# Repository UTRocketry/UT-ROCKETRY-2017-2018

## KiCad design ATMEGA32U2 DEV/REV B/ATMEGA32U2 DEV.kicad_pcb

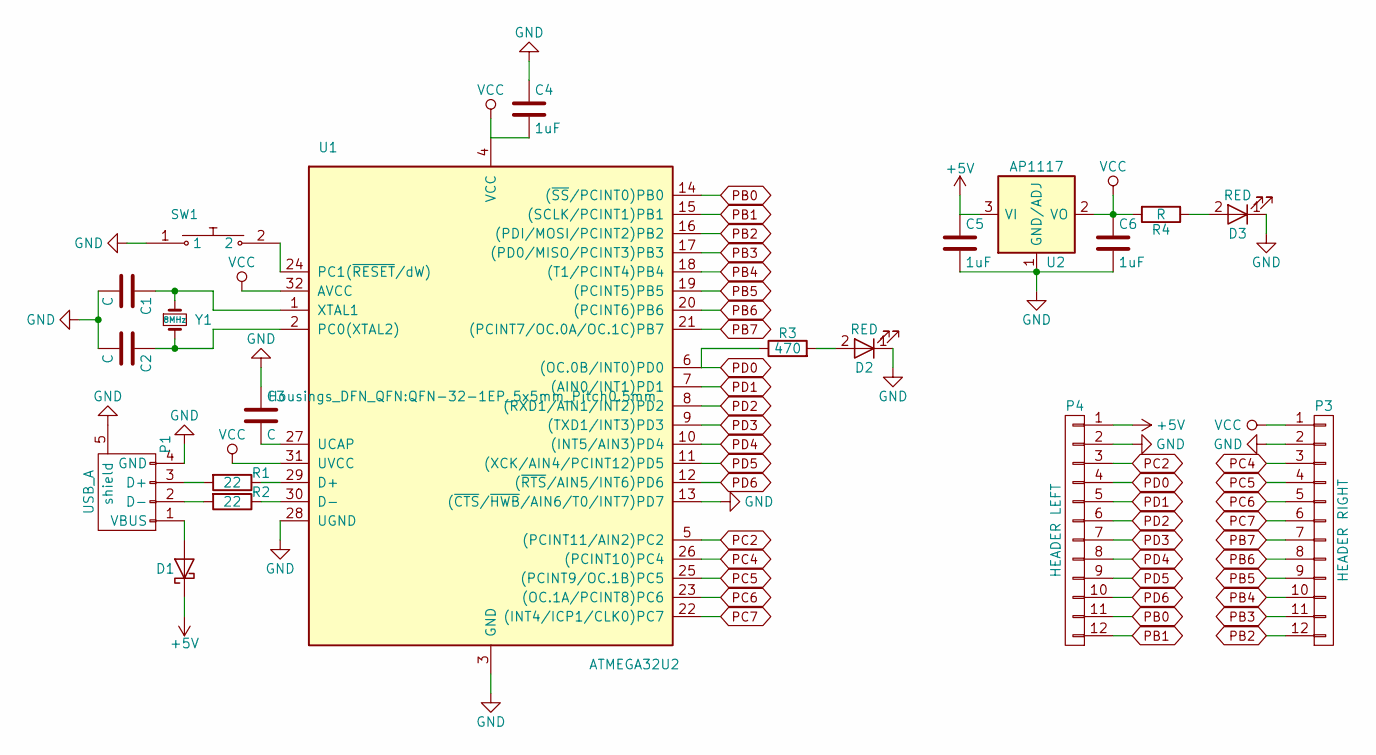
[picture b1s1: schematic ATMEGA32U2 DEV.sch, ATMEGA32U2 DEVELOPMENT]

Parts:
C1, C2, C3: C; C_0603
C4, C5, C6: 1uF; C_0603
D1: D_Schottky; D_SOD-323F
D2, D3: RED; LED_0603
P1: USB_A; USB_Micro-B_Molex_47346-0001
P3: HEADER RIGHT; Pin_Header_Straight_1x12
P4: HEADER LEFT; Pin_Header_Straight_1x12
R1, R2: 22; R_0603
R3: 470; R_0603
R4: R; R_0603
SW1: Push_SW; PTS810 SJK 250 SMTR LFS
U1: ATMEGA32U2; QFN-32-1EP_5x5mm_Pitch0.5mm
U2: AP1117; SOT-23
Y1: 8MHz; ABM3

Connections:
+5V: C5.1, D1.1 (K), P4.1, U2.3 (VI)
GND: C1.2, C2.2, C3.1, C4.1, C5.2, C6.2, D2.1 (K), D3.1 (K), P1.4 (GND), P1.5 (shield), P3.2, P4.2, SW1.1, U1.3 (GND), U1.13 ((~CTS~/~HWB~/AIN6/T0/INT7)PD7), U1.28 (UGND), U2.1 (GND/ADJ)
unnamed: C1.1, U1.1 (XTAL1), Y1.1
unnamed: C2.1, U1.2 (PC0(XTAL2)), Y1.2
unnamed: C3.2, U1.27 (UCAP)
unnamed: D1.2 (A), P1.1 (VBUS)
unnamed: D2.2 (A), R3.2
unnamed: D3.2 (A), R4.1
unnamed: P1.2 (D-), R2.2
unnamed: P1.3 (D+), R1.2
unnamed: R1.1, U1.29 (D+)
unnamed: R2.1, U1.30 (D-)
unnamed: SW1.2, U1.24 (PC1(~RESET~/dW))
PB0: P4.11, U1.14 ((~SS~/PCINT0)PB0)
PB1: P4.12, U1.15 ((SCLK/PCINT1)PB1)
PB2: P3.12, U1.16 ((PDI/MOSI/PCINT2)PB2)
PB3: P3.11, U1.17 ((PD0/MISO/PCINT3)PB3)
PB4: P3.10, U1.18 ((T1/PCINT4)PB4)
PB5: P3.9, U1.19 ((PCINT5)PB5)
PB6: P3.8, U1.20 ((PCINT6)PB6)
PB7: P3.7, U1.21 ((PCINT7/OC.0A/OC.1C)PB7)
PC2: P4.3, U1.5 ((PCINT11/AIN2)PC2)
PC4: P3.3, U1.26 ((PCINT10)PC4)
PC5: P3.4, U1.25 ((PCINT9/OC.1B)PC5)
PC6: P3.5, U1.23 ((OC.1A/PCINT8)PC6)
PC7: P3.6, U1.22 ((INT4/ICP1/CLK0)PC7)
PD0: P4.4, R3.1, U1.6 ((OC.0B/INT0)PD0)
PD1: P4.5, U1.7 ((AIN0/INT1)PD1)
PD2: P4.6, U1.8 ((RXD1/AIN1/INT2)PD2)
PD3: P4.7, U1.9 ((TXD1/INT3)PD3)
PD4: P4.8, U1.10 ((INT5/AIN3)PD4)
PD5: P4.9, U1.11 ((XCK/AIN4/PCINT12)PD5)
PD6: P4.10, U1.12 ((~RTS~/AIN5/INT6)PD6)
VCC: C4.2, C6.1, P3.1, R4.2, U1.4 (VCC), U1.31 (UVCC), U1.32 (AVCC), U2.2 (VO), U2.4 (VO)

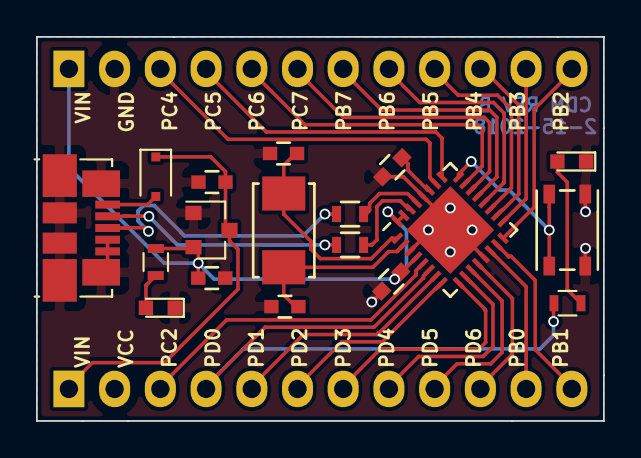
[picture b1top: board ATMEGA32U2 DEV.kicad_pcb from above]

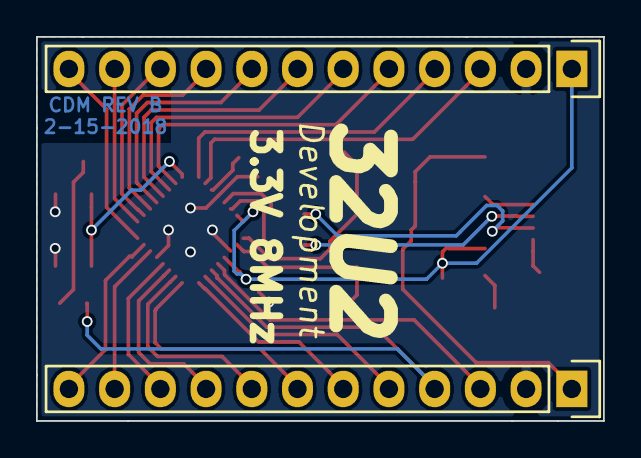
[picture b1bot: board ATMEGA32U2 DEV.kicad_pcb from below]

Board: 2 copper layers, 31.5 x 21.3 mm, 20 parts (2 on the bottom side), 34 nets.

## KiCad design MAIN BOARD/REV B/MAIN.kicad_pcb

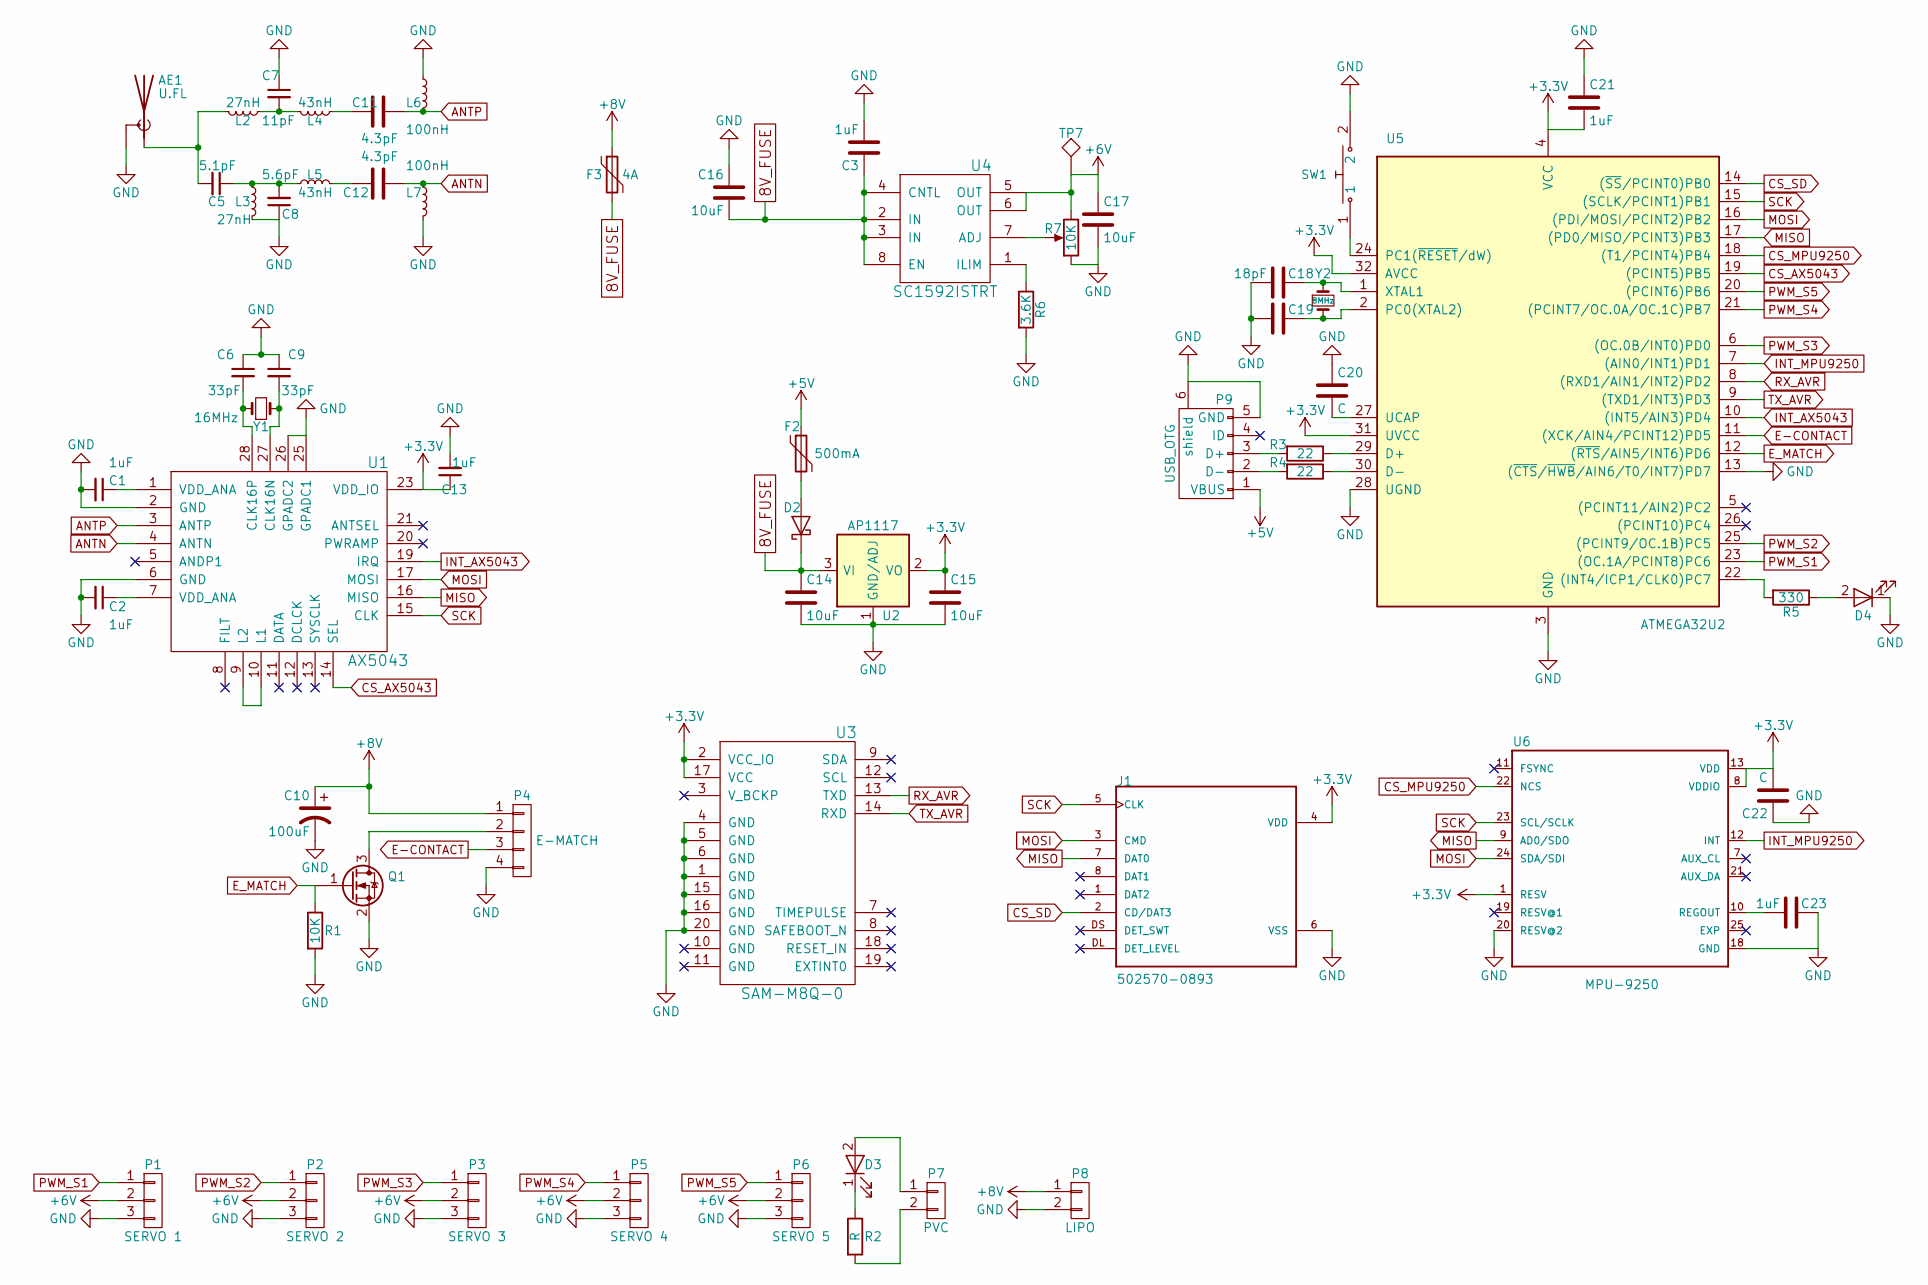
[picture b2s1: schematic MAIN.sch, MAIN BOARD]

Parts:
AE1: U.FL; U.FL-COAX
C1, C2, C3, C13, C21, C23: 1uF; C_0402
C5: 5.1pF; C_0402
C6, C9: 33pF; C_0402
C7: 11pF; C_0402
C8: 5.6pF; C_0402
C10: 100uF; C_0603
C11, C12: 4.3pF; C_0402
C14, C15, C16, C17: 10uF; C_0603
C18: 18pF; C_0402
C19, C20, C22: C; C_0402
D2: D_Schottky; D_SOD-123F
D3, D4: LED; LED_0402
F2: 500mA; C_1206
F3: 4A; C_1206
J1: 502570-0893; MOLEX_502570-0893
L2, L3: 27nH; C_0402
L4, L5: 43nH; C_0402
L6, L7: 100nH; C_0402
P1: SERVO 1; Pin_Header_Straight_1x03_Pitch2.54mm
P2: SERVO 2; Pin_Header_Straight_1x03_Pitch2.54mm
P3: SERVO 3; Pin_Header_Straight_1x03_Pitch2.54mm
P4: E-MATCH; TE1X4
P5: SERVO 4; Pin_Header_Straight_1x03_Pitch2.54mm
P6: SERVO 5; Pin_Header_Straight_1x03_Pitch2.54mm
P7: PVC; TE1X2
P8: LIPO; TE1X2
P9: USB_OTG; 0473461001_GLUE
Q1: Q_NMOS_GSD; SOT-23
R1: 10K; R_0402
R2: R; R_0402
R3, R4: 22; R_0402
R5: 330; R_0402
R6: 3.6K; R_0402
R7: 10K; Potentiometer_Trimmer-EVM3E
SW1: Push_SW; KXT 131 LHS
TP7: TEST; Measurement_Point_Round-SMD-Pad_Small
U1: AX5043; QFN-28-1EP_5x5mm_Pitch0.5mm
U2: AP1117; SOT-23
U3: SAM-M8Q-0
U4: SC1592ISTRT; SOIC-8-1EP_3.9x4.9mm_Pitch1.27mm
U5: ATMEGA32U2; QFN-32-1EP_5x5mm_Pitch0.5mm
U6: MPU-9250; QFN40P300X300X105-25N
Y1: 16MHz; Crystal_SMD_Abracon_ABM3-2pin_5.0x3.2mm
Y2: 8MHz; Crystal_SMD_Abracon_ABM3-2pin_5.0x3.2mm

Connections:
8V_FUSE: C3.1, C14.1, C16.2, D2.1 (K), F3.2, U2.3 (VI), U4.2 (IN), U4.3 (IN), U4.4 (CNTL), U4.8 (EN)
+3V3: C13.1, C15.1, C21.2, C22.2, J1.4 (VDD), U1.23 (VDD_IO), U2.2 (VO), U2.4 (VO), U3.2 (VCC_IO), U3.17 (VCC), U5.4 (VCC), U5.31 (UVCC), U5.32 (AVCC), U6.1 (RESV), U6.8 (VDDIO), U6.13 (VDD); also elsewhere on the board
+5V: F2.1, P9.1 (VBUS)
+6V: C17.1, P1.2, P2.2, P3.2, P5.2, P6.2, R7.3, TP7.1, U4.5 (OUT), U4.6 (OUT)
+8V: C10.1, F3.1, P4.1, P8.1
ANTN: C12.1, L7.2, U1.4 (ANTN)
ANTP: C11.1, L6.2, U1.3 (ANTP)
CS_AX5043: U1.14 (SEL), U5.19 ((PCINT5)PB5)
CS_MPU9250: U5.18 ((T1/PCINT4)PB4), U6.22 (NCS)
CS_SD: J1.2 (CD/DAT3), U5.14 ((~SS~/PCINT0)PB0)
E-CONTACT: P4.3, U5.11 ((XCK/AIN4/PCINT12)PD5)
E_MATCH: Q1.1 (G), R1.1, U5.12 ((~RTS~/AIN5/INT6)PD6)
GND: AE1.2 (Shield), C1.2, C2.2, C3.2, C6.1, C7.1, C8.1, C9.1, C10.2, C13.2, C14.2, C15.2, C16.1, C17.2, C18.2, C19.2, C20.1, C21.1, C22.1, C23.1, D4.1 (K), J1.6 (VSS), L3.1, L6.1, L7.1, P1.3, P2.3, P3.3, P4.4, P5.3, P6.3, P8.2, P9.5 (GND), P9.6 (shield), Q1.2 (S), R1.2, R6.2, R7.1, SW1.2, U1.2 (GND), U1.6 (GND), U1.25 (GPADC1), U1.26 (GPADC2), U2.1 (GND/ADJ), U3.1 (GND), U3.4 (GND), U3.5 (GND), U3.6 (GND), U3.15 (GND), U3.16 (GND), U3.20 (GND), U4.9, U5.3 (GND), U5.13 ((~CTS~/~HWB~/AIN6/T0/INT7)PD7), U5.28 (UGND), U6.18 (GND), U6.20 (RESV@2)
INT_AX5043: U1.19 (IRQ), U5.10 ((INT5/AIN3)PD4)
INT_MPU9250: U5.7 ((AIN0/INT1)PD1), U6.12 (INT)
MISO: J1.7 (DAT0), U1.16 (MISO), U5.17 ((PD0/MISO/PCINT3)PB3), U6.9 (AD0/SDO)
MOSI: J1.3 (CMD), U1.17 (MOSI), U5.16 ((PDI/MOSI/PCINT2)PB2), U6.24 (SDA/SDI)
unnamed: AE1.1 (A), C5.2, L2.2
unnamed: C1.1, U1.1 (VDD_ANA)
unnamed: C2.1, U1.7 (VDD_ANA)
unnamed: C5.1, C8.2, L3.2, L5.2
unnamed: C6.2, U1.28 (CLK16P), Y1.1
unnamed: C7.2, L2.1, L4.2
unnamed: C9.2, U1.27 (CLK16N), Y1.2
unnamed: C11.2, L4.1
unnamed: C12.2, L5.1
unnamed: C18.1, U5.1 (XTAL1), Y2.1
unnamed: C19.1, U5.2 (PC0(XTAL2)), Y2.2
unnamed: C20.2, U5.27 (UCAP)
unnamed: C23.2, U6.10 (REGOUT)
unnamed: D2.2 (A), F2.2
unnamed: D3.1 (K), R2.1
unnamed: D3.2 (A), P7.1
unnamed: D4.2 (A), R5.1
unnamed: P4.2, Q1.3 (D)
unnamed: P7.2, R2.2
unnamed: P9.2 (D-), R4.2
unnamed: P9.3 (D+), R3.2
unnamed: R3.1, U5.29 (D+)
unnamed: R4.1, U5.30 (D-)
unnamed: R5.2, U5.22 ((INT4/ICP1/CLK0)PC7)
unnamed: R6.1, U4.1 (ILIM)
unnamed: R7.2, U4.7 (ADJ)
unnamed: SW1.1, U5.24 (PC1(~RESET~/dW))
unnamed: U1.9 (L2), U1.10 (L1)
PWM_S1: P1.1, U5.23 ((OC.1A/PCINT8)PC6)
PWM_S2: P2.1, U5.25 ((PCINT9/OC.1B)PC5)
PWM_S3: P3.1, U5.6 ((OC.0B/INT0)PD0)
PWM_S4: P5.1, U5.21 ((PCINT7/OC.0A/OC.1C)PB7)
PWM_S5: P6.1, U5.20 ((PCINT6)PB6)
RX_AVR: U3.13 (TXD), U5.8 ((RXD1/AIN1/INT2)PD2)
SCK: J1.5 (CLK), U1.15 (CLK), U5.15 ((SCLK/PCINT1)PB1), U6.23 (SCL/SCLK)
TX_AVR: U3.14 (RXD), U5.9 ((TXD1/INT3)PD3)

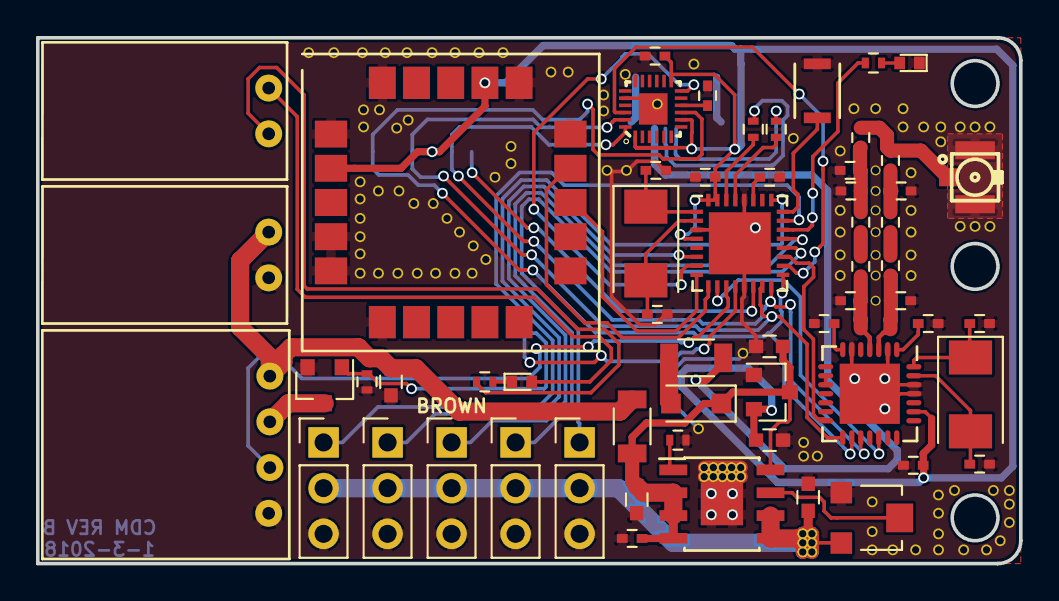
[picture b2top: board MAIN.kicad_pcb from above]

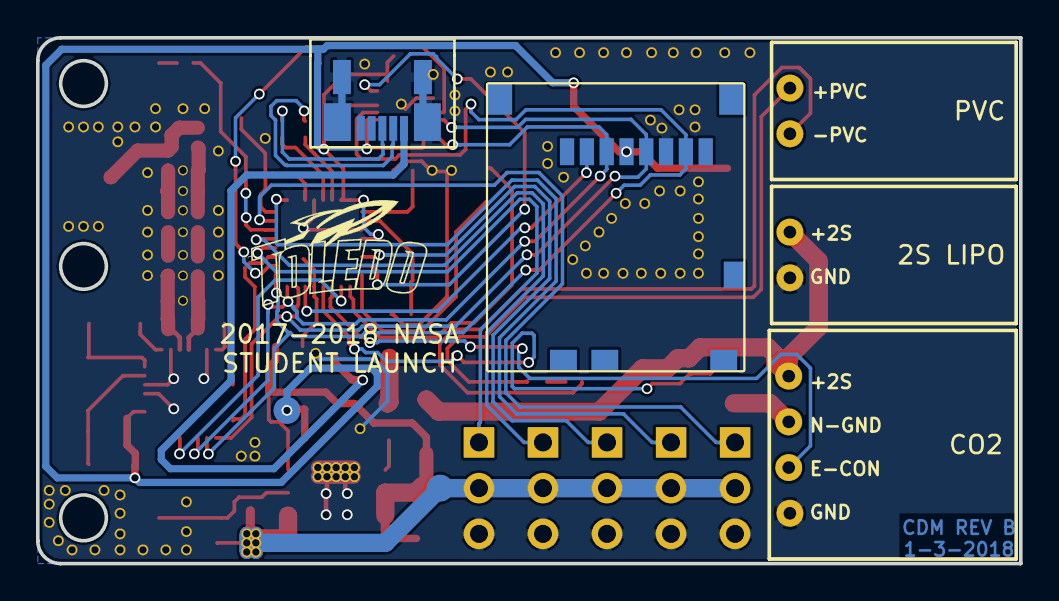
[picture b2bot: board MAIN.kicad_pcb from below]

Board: 2 copper layers, 54.6 x 29.2 mm, 63 parts (4 on the bottom side), 53 nets.

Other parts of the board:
TP4: TEST; Measurement_Point_Round-SMD-Pad_Small

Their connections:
+3V3: TP4.1; also elsewhere on the board

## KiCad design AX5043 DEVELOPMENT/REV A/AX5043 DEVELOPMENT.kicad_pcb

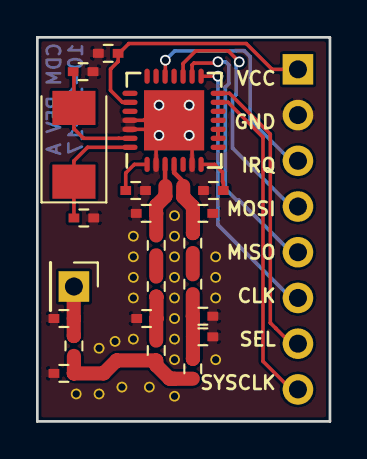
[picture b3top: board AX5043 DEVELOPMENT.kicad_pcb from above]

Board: 2 copper layers, 16.3 x 21.3 mm, 23 parts (1 on the bottom side), 21 nets.

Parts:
AE1: Antenna; Pin_Header_Straight_1x01_Pitch2.54mm
C1: 151pF; C_0402
C2: 129pF; C_0402
C3, C4: 33pF; C_0402
C5, C13, C14: 1uF; C_0402
C6: 5.1pF; C_0402
C7: 11pF; C_0402
C8: 5.6pF; C_0402
C9, C10: 4.3pF; C_0402
L1: .002uH; C_0402
L3, L4: 27nH; C_0402
L5, L6: 43nH; C_0402
L7, L8: 100nH; C_0402
P1: CONN_01X08; Pin_Header_Straight_1x08_Pitch2.54mm
U1: AX5043; QFN-28-1EP_5x5mm_Pitch0.5mm
Y1: 16MHz; Crystal_SMD_Abracon_ABM3-2pin_5.0x3.2mm

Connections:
ANTN: C10.1, L8.2, U1.4
ANTP: C9.1, L7.2, U1.3
CLK: P1.6, U1.15
GND: C1.1, C2.2, C3.1, C4.1, C5.2, C7.1, C8.1, C13.2, C14.2, L4.1, L7.1, L8.1, P1.2, U1.2, U1.6, U1.25, U1.26, U1.29
IRQ: P1.3, U1.19
MISO: P1.5, U1.16
MOSI: P1.4, U1.17
unnamed: AE1.1, C1.2, L1.2
unnamed: C2.1, C6.2, L1.1, L3.2
unnamed: C3.2, U1.28, Y1.1
unnamed: C4.2, U1.27, Y1.2
unnamed: C6.1, C8.2, L4.2, L6.2
unnamed: C7.2, L3.1, L5.2
unnamed: C9.2, L5.1
unnamed: C10.2, L6.1
unnamed: C13.1, U1.1
unnamed: C14.1, U1.7
unnamed: U1.9, U1.10
SEL: P1.7, U1.14
SYSCLK: P1.8, U1.13
VCC: C5.1, P1.1, U1.23

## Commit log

2018-01-10 added E-MATCH
2018-02-15 REV B Pogo
2018-03-03 REV B of POGO
2018-03-03 POGO REV C
